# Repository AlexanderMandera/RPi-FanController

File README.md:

# RPi-FanController

[![Upload to  - 
AISLER](https://img.shields.io/badge/Upload_to_-AISLER-ff8000)](https://aisler.net/p/new?url=https://raw.githubusercontent.com/AlexanderMandera/RPi-FanController/master/RPi-FanController.kicad_pcb&ref=github)

A simple fan controller that uses GPIO 14 to control a two-pin DC 5V fan.

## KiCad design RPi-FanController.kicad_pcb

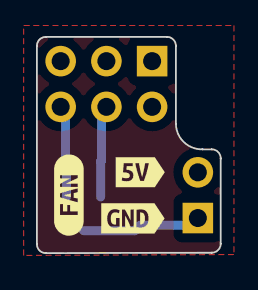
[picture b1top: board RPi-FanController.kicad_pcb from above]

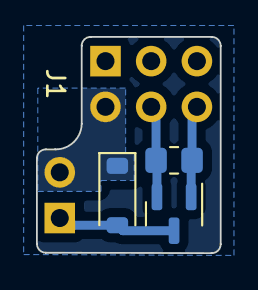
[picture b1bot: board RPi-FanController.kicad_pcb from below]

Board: 2 copper layers, 10.2 x 12.0 mm, 8 parts (4 on the bottom side), 4 nets.

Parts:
D1: SOD123; D_SOD-123
FAN1: PinHeader_1x02_P2.54mm_Vertical
J1: RPi; PinSocket_2x03_P2.54mm_Vertical
Q1: IRLML2502; SOT-23
R2: 10k; R_0805_2012Metric_Pad1.20x1.40mm_HandSolder
kibuzzard-64B3D6D5: G***; kibuzzard-64B3D6D5
kibuzzard-64B3D6E3: G***; kibuzzard-64B3D6E3
kibuzzard-64B3D766: G***; kibuzzard-64B3D766

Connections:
+5V: D1.1 (K), FAN1.2, J1.2
/FAN_GPIO: J1.6, Q1.1 (G), R2.2
GND: J1.4, Q1.2 (S), R2.1
unnamed: D1.2 (A), FAN1.1, Q1.3 (D)
